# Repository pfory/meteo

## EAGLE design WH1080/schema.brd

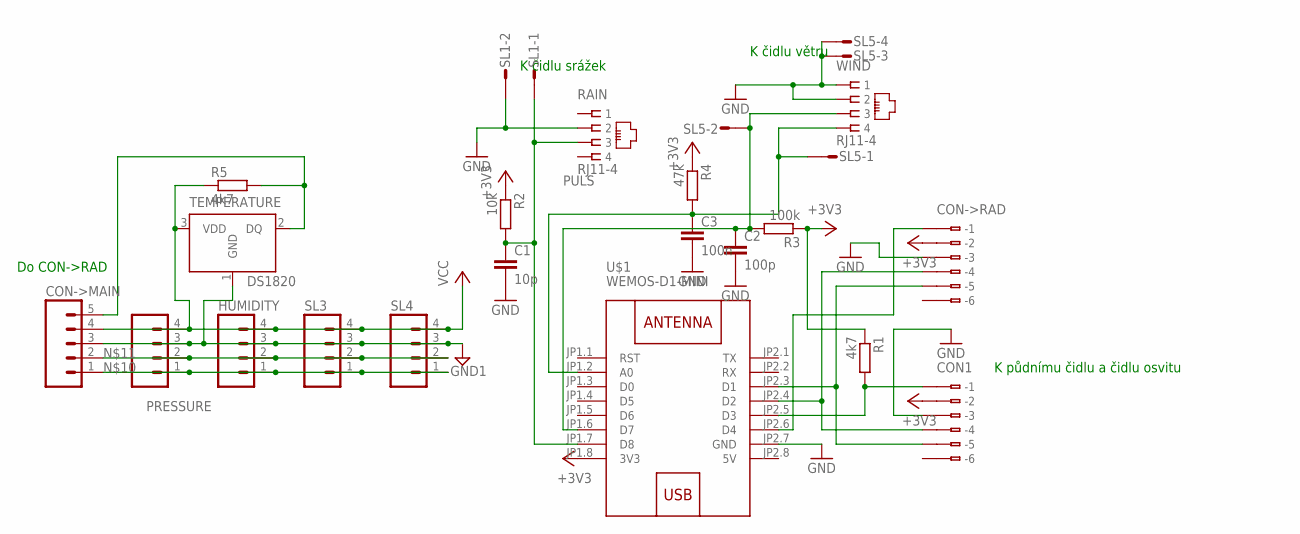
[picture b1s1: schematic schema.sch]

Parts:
C1: 10p; C025-024X044
C2: 100p; C025-024X044
C3: 100n; C025-024X044
CON1: 233-506
CON->MAIN: M05; 05P
CON->RAD: 233-506
HUMIDITY: M04; 04P
PRESSURE: M04; 04P
R1, R5: 4k7; 0204/7
R2: 10k; 0204/7
R3: 100k; 0204/7
R4: 47k; 0204/7
RAIN: RJ11-4
SL1: M02S; 02P
SL3, SL4: M04; 04P
SL5: M04S; 04P
TEMPERATURE: DS1820; TO-92
U$1: WEMOS-D1-MINI
WIND: RJ11-4

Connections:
5V: U$1.JP2.8 (5V)
+3V3: CON1.B2 (B-2), CON->RAD.B2 (B-2), R1.1, R2.1, R3.1, R4.1, U$1.JP1.8 (3V3)
GND: C1.2, C2.2, C3.2, CON1.B3 (B-3), CON->RAD.B3 (B-3), RAIN.2, SL1.2, SL5.3, SL5.4, U$1.JP2.7 (GND), WIND.1, WIND.2
GND1: CON->MAIN.3, HUMIDITY.3, PRESSURE.3, SL3.3, SL4.3, TEMPERATURE.1 (GND)
unnamed: CON->MAIN.5, R5.2, TEMPERATURE.2 (DQ)
unnamed: CON->MAIN.1, HUMIDITY.1, PRESSURE.1, SL3.1, SL4.1
unnamed: CON->MAIN.2, HUMIDITY.2, PRESSURE.2, SL3.2, SL4.2
unnamed: CON1.B1 (B-1), R1.2, U$1.JP2.5 (D3)
unnamed: CON->RAD.B1 (B-1), U$1.JP2.6 (D4)
PULS: C1.1, R2.2, RAIN.3, SL1.1, U$1.JP1.7 (D8)
RYCHLOST: C2.1, R3.2, SL5.2, U$1.JP1.6 (D7), WIND.3
SCL: CON1.B5 (B-5), CON->RAD.B5 (B-5), U$1.JP2.3 (D1)
SDA: CON1.B4 (B-4), CON->RAD.B4 (B-4), U$1.JP2.4 (D2)
SMER: C3.1, R4.2, SL5.1, U$1.JP1.2 (A0), WIND.4
VCC: CON->MAIN.4, HUMIDITY.4, PRESSURE.4, R5.1, SL3.4, SL4.4, TEMPERATURE.3 (VDD)

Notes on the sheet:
K čidlu srážek
K čidlu větru
Do CON->RAD
K půdnímu čidlu a čidlu osvitu

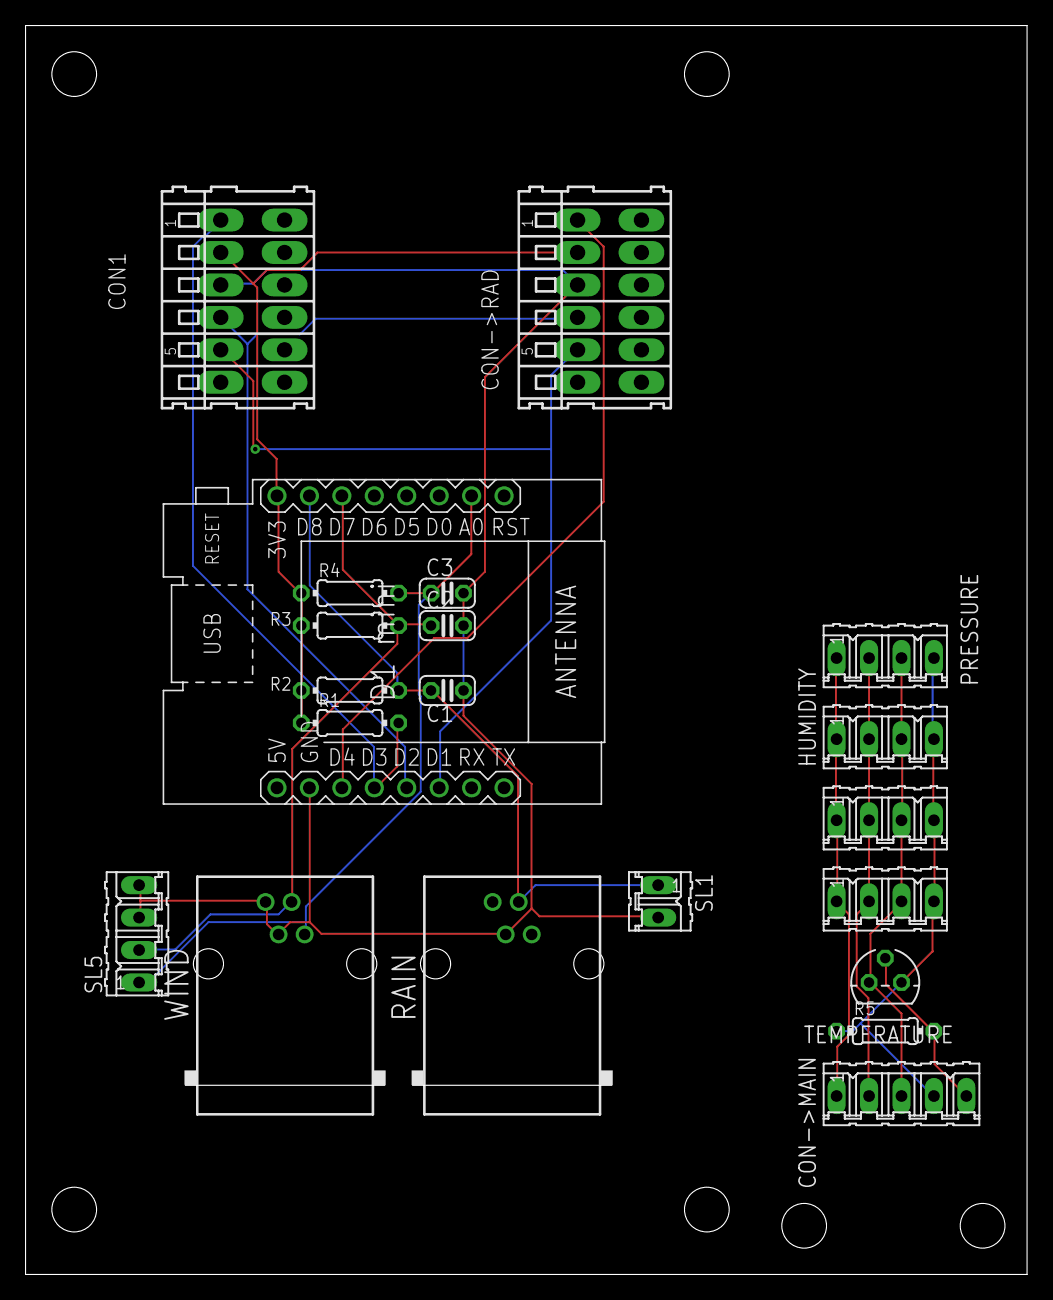
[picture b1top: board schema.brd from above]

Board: 2 copper layers, 78.4 x 97.8 mm, 21 parts (0 on the bottom side), 14 nets.

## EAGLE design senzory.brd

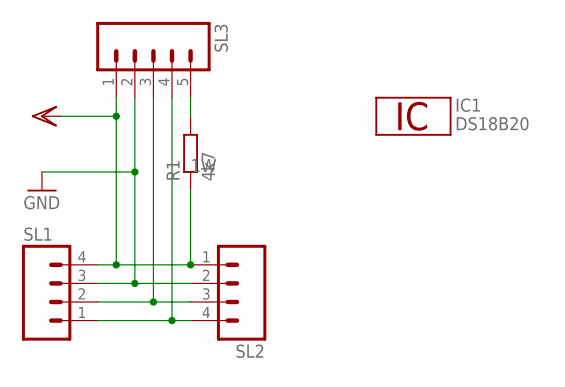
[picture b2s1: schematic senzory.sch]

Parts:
IC1: DS18B20; TO92-
R1: 4k7; 0204/7
SL1, SL2: M04; 04P
SL3: M05; 05P

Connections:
1W: IC1.2 (1W), R1.2, SL3.5
GND: IC1.1 (GND), SL1.3, SL2.2, SL3.2
SCL: SL1.2, SL2.3, SL3.3
SDA: SL1.1, SL2.4, SL3.4
VDD: IC1.3 (VDD), R1.1, SL1.4, SL2.1, SL3.1

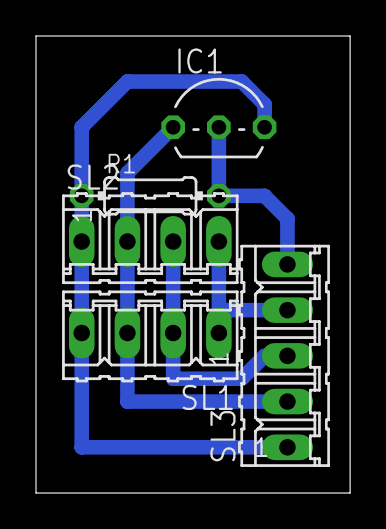
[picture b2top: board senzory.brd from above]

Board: 2 copper layers, 17.4 x 25.4 mm, 5 parts (0 on the bottom side), 5 nets.

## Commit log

2016-06-24 v1,3
2016-07-28 pi na chate
2018-01-06 náhrada odesílání na Xively - lokální webserver
2018-01-07 pripraveno na nasazeni
2018-01-07 DALLAS na D10
2018-01-08 uprava OTA
2018-01-08 formatovani a zmeny define
2018-01-08 jeste doladit verzi pro MEGA2560
2018-01-09 verze nasazena 9.1.2018
2018-01-21 oprava zobrazení teplot html
2018-01-22 oprava teplot 0 až -1 v html
2018-01-22 konečně správný výstup teplot do html
2018-03-27 letni/zimni cas
2018-03-28 +library SI7021-master.zip
2018-05-28 restart code
2018-06-14 + hb
2018-06-14 v1.61
2018-06-14 popis a prikaz pro OTA update
2018-06-15 oprava typu hb
2018-06-15 1.92
2018-07-10 kosmeticke upravy kodu
2018-07-11 v0.64 - uprava casovani - vyreseni problemu s restartem
2018-08-13 AutoconnectAP -> Meteo
2018-08-13 v1.65
2018-08-27 1.67 timeout
2018-08-27 v0.67
2018-09-01 1.68 sledovani napeti
2018-09-23 -pri nefunkcim internet nelze nastavit cas
2018-09-24 1.69
2018-10-10 zmena prihlaseni k wifi, AP mode jen pokud nezískám SSID
2018-10-24 sender objekt
2018-10-28 v1.8
2018-10-29 + folder bin a přesun binárek sem
2018-10-29 1.81
2019-03-07 json 6
2019-03-07 v1.81
2019-03-07 -sender
2019-06-20 - vynuceny reset pres MQTT
2019-07-21 reset kdyz nemeri cidla na i2c
2019-08-06 1.92 - upraveny podminky pro restart
2019-08-07 +desky
2019-08-12 + reset reason
2019-08-28 + diagnostika programového resetu, stav 998 a 999
2019-09-08 rozliseni duvodu resetu
2019-09-10 oprava chyboveho stavu
2019-09-10 verze
2019-10-10 1.95 modernizace kodu
2019-10-10 send delay 1 minuta
2019-10-10 1.97
2020-05-06 1.98 - tlak na in-pocasi v hPa
2021-01-21 - nepouzivane define z configu
2021-01-21 + double reset detector + ip z dhcp uprava wifi connectoru na novy tvar
2021-01-21 uprava nazvu
2021-04-12 2.00
2021-11-30 v 2.10 + config
2021-12-02 v2.1
2021-12-02 v2.11
2021-12-07 v2.23
2023-08-07 změna intervalu měření z 5 sekund na 30 sekund
2023-08-07 kosmetické změny kódu
2023-12-07 SHT40
2023-12-10 + sensor vlhkosti SHT40
2024-01-22 pridani dat do vystupu na inPocasi a zmena formatu dat
2024-01-23 + data vítr a srážky pro in-pocasi.cz
2024-01-26 nova meteo stanice
2024-03-21 vyroba DPS
2024-04-10 změna odporu pro dělič směru větru
2024-04-15 filtr srazky
2024-04-17 zmena mqtt_base
2024-05-07 odesilani pulsu srazek jen pokud > 0
2024-06-26 ostrá verze
2024-08-28 převedeno na Tasmota
